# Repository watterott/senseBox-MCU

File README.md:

# senseBox MCU
senseBox MCU is a Microchip SAMD21 based open-source board for sensors.

* [Microchip ATSAMD21](https://www.microchip.com/wwwproducts/en/ATSAMD21G18) ARM Cortex-M0+ Microcontroller
* [Microchip ATECC608A](https://www.microchip.com/wwwproducts/en/ATECC608A) Crypto Authentication
* [Bosch BMX055](https://www.bosch-sensortec.com/bst/products/all_products/bmx055) Orientation Sensor (Accelerometer + Gyroscope + Magnetometer)
* USB CDC+MSC Bootloader (Arduino compatible)
* XBee compatible sockets (with UART and SPI)
* 5V tolerant IOs, UART, I2C (JST-PH connectors)
* MicroUSB connector for power and data
* Idle power consumption about 20mA (single 5V power supply)
* Open-Source
* **[Documentation on learn.watterott.com](https://learn.watterott.com)**

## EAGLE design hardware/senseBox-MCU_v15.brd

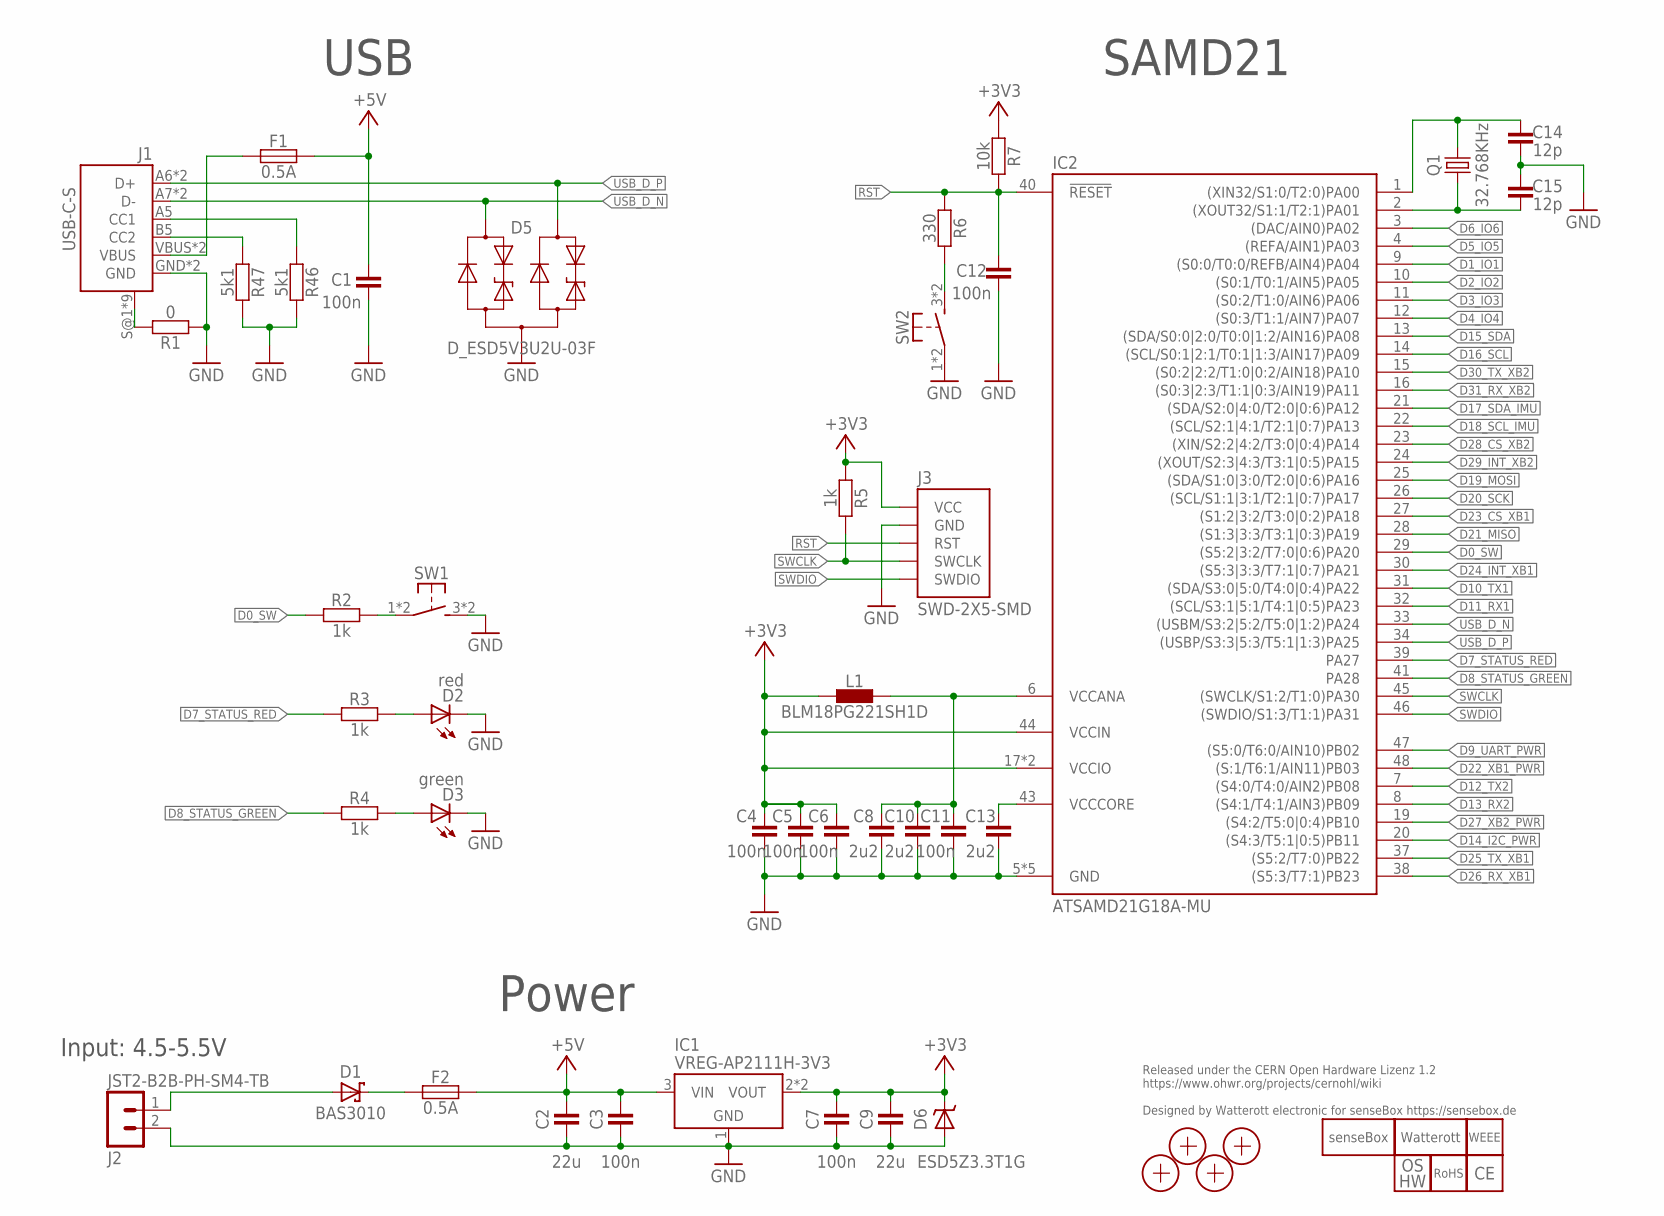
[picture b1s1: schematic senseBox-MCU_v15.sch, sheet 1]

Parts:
C1, C3, C4, C5, C6, C7, C11, C12: 100n; C0402
C2, C9: 22u; C0805
C8, C10, C13: 2u2; C0402
C14, C15: 12p; C0402
D1: BAS3010; SOD323
D2: red; C0603
D3: green; C0603
D5: D_ESD5V3U2U-03F; SOT723
D6: ESD5Z3.3T1G; SOD523
F1, F2: 0.5A; C0805
IC1: VREG-AP2111H-3V3; SOT223
IC2: ATSAMD21G18A-MU; QFN48-PAD
J1: USB-C-S
J2: JST2-B2B-PH-SM4-TB; JST_B2B-PH-SM4-TB
J3: SWD-2X5-SMD; SWD-2X5_SMD
L1: BLM18PG221SH1D; C0603
LOGO1: LOGO_SENSEBOX-12; SB_12MM
LOGO3: OSHW_LOGOX0070; OSHW_3MM
LOGO4: LOGO_SPARK-4; SPARK_4MM
LOGO5: LOGO_ROHS-4; ROHS_4MM
LOGO6: LOGO_WEEE-4; WEEE_4MM
LOGO7: LOGO_CE-4; CE_4MM
Q1: 32.768KHz; CRYSTAL_ZM315
R1: 0; C0402
R2, R3, R4, R5: 1k; C0402
R6: 330; C0402
R7: 10k; C0402
R46, R47: 5k1; C0402
SW1: PTS645SH50SMTR92-Grey; SW6X6_SMD
SW2: PTS645SK50SMTR92-Red; SW6X6_SMD
X1, X2, X3, X4: PASSER-07; PASSER_07MM

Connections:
+3V3: C4.2, C5.2, C6.2, C7.2, C9.2, D6.C, IC1.2 (VOUT), IC1.4 (VOUT), IC2.17 (VCCIO), IC2.36 (VCCIO), IC2.44 (VCCIN), J3.VCC, L1.1, R5.1, R7.1; also elsewhere on the board
+5V: C1.2, C2.2, C3.2, F1.2, F2.2, IC1.3 (VIN); also elsewhere on the board
CC1: J1.A5 (CC1), R46.1
CC2: J1.B5 (CC2), R47.1
D0_SW: IC2.29 ((S5:2|3:2/T7:0|0:6)PA20), R2.1
D1_IO1: IC2.9 ((S0:0/T0:0/REFB/AIN4)PA04); also elsewhere on the board
D2_IO2: IC2.10 ((S0:1/T0:1/AIN5)PA05); also elsewhere on the board
D3_IO3: IC2.11 ((S0:2/T1:0/AIN6)PA06); also elsewhere on the board
D4_IO4: IC2.12 ((S0:3/T1:1/AIN7)PA07); also elsewhere on the board
D5_IO5: IC2.4 ((REFA/AIN1)PA03); also elsewhere on the board
D6_IO6: IC2.3 ((DAC/AIN0)PA02); also elsewhere on the board
D7_STATUS_RED: IC2.39 (PA27), R3.1
D8_STATUS_GREEN: IC2.41 (PA28), R4.1
D9_UART_PWR: IC2.47 ((S5:0/T6:0/AIN10)PB02); also elsewhere on the board
D10_TX1: IC2.31 ((SDA/S3:0|5:0/T4:0|0:4)PA22); also elsewhere on the board
D11_RX1: IC2.32 ((SCL/S3:1|5:1/T4:1|0:5)PA23); also elsewhere on the board
D12_TX2: IC2.7 ((S4:0/T4:0/AIN2)PB08); also elsewhere on the board
D13_RX2: IC2.8 ((S4:1/T4:1/AIN3)PB09); also elsewhere on the board
D14_I2C_PWR: IC2.20 ((S4:3/T5:1|0:5)PB11); also elsewhere on the board
D15_SDA: IC2.13 ((SDA/S0:0|2:0/T0:0|1:2/AIN16)PA08); also elsewhere on the board
D16_SCL: IC2.14 ((SCL/S0:1|2:1/T0:1|1:3/AIN17)PA09); also elsewhere on the board
D17_SDA_IMU: IC2.21 ((SDA/S2:0|4:0/T2:0|0:6)PA12); also elsewhere on the board
D18_SCL_IMU: IC2.22 ((SCL/S2:1|4:1/T2:1|0:7)PA13); also elsewhere on the board
D19_MOSI: IC2.25 ((SDA/S1:0|3:0/T2:0|0:6)PA16); also elsewhere on the board
D20_SCK: IC2.26 ((SCL/S1:1|3:1/T2:1|0:7)PA17); also elsewhere on the board
D21_MISO: IC2.28 ((S1:3|3:3/T3:1|0:3)PA19); also elsewhere on the board
D22_!XB1_PWR: IC2.48 ((S:1/T6:1/AIN11)PB03); also elsewhere on the board
D23_CS_XB1: IC2.27 ((S1:2|3:2/T3:0|0:2)PA18); also elsewhere on the board
D24_INT_XB1: IC2.30 ((S5:3|3:3/T7:1|0:7)PA21); also elsewhere on the board
D25_TX_XB1: IC2.37 ((S5:2/T7:0)PB22); also elsewhere on the board
D26_RX_XB1: IC2.38 ((S5:3/T7:1)PB23); also elsewhere on the board
D27_!XB2_PWR: IC2.19 ((S4:2/T5:0|0:4)PB10); also elsewhere on the board
D28_CS_XB2: IC2.23 ((XIN/S2:2|4:2/T3:0|0:4)PA14); also elsewhere on the board
D29_INT_XB2: IC2.24 ((XOUT/S2:3|4:3/T3:1|0:5)PA15); also elsewhere on the board
D30_TX_XB2: IC2.15 ((S0:2|2:2/T1:0|0:2/AIN18)PA10); also elsewhere on the board
D31_RX_XB2: IC2.16 ((S0:3|2:3/T1:1|0:3/AIN19)PA11); also elsewhere on the board
GND: C1.1, C2.1, C3.1, C4.1, C5.1, C6.1, C7.1, C8.1, C9.1, C10.1, C11.1, C12.1, C13.1, C14.2, C15.1, D2.C, D3.C, D5.3 (A), D6.A, IC1.1 (GND), IC2.5 (GND), IC2.18 (GND), IC2.35 (GND), IC2.42 (GND), IC2.TP (GND), J1.GND, J1.GND2 (GND), J2.2, J3.GND@1 (GND), J3.GND@2 (GND), J3.GND@3 (GND), R1.1, R46.2, R47.2, SW1.3 (S1), SW1.4 (S1), SW2.1, SW2.2 (P1); also elsewhere on the board
unnamed: C14.1, IC2.1 ((XIN32/S1:0/T2:0)PA00), Q1.2
unnamed: C15.2, IC2.2 ((XOUT32/S1:1/T2:1)PA01), Q1.1
unnamed: D2.A, R3.2
unnamed: D3.A, R4.2
unnamed: R6.2, SW2.3 (S1), SW2.4 (S1)
RST: C12.2, IC2.40 (!RESET), J3.RST, R6.1, R7.2
SHLD: J1.S@1 (SHIELD), J1.S@2 (SHIELD), J1.S@3 (SHIELD), J1.S@4 (SHIELD), J1.S@5 (SHIELD), J1.S@6 (SHIELD), J1.S@7 (SHIELD), J1.S@8 (SHIELD), J1.S@9 (SHIELD), R1.2
SW: R2.2, SW1.1, SW1.2 (P1)
SWCLK: IC2.45 ((SWCLK/S1:2/T1:0)PA30), J3.SWCLK, R5.2
SWDIO: IC2.46 ((SWDIO/S1:3/T1:1)PA31), J3.SWDIO
USB_D_N: D5.1 (C1), IC2.33 ((USBM/S3:2|5:2/T5:0|1:2)PA24), J1.A7 (D-), J1.B7 (D-)
USB_D_P: D5.2 (C2), IC2.34 ((USBP/S3:3|5:3/T5:1|1:3)PA25), J1.A6 (D+), J1.B6 (D+)
V5V: D1.C, F2.1
VBUS: F1.1, J1.VBUS, J1.VBUS2 (VBUS)
VCCANA: C8.2, C10.2, C11.2, IC2.6 (VCCANA), L1.2
VCCCORE: C13.2, IC2.43 (VCCCORE)
VIN: D1.A, J2.1

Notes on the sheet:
Released under the CERN Open Hardware Lizenz 1.2 https://www.ohwr.org/projects/cernohl/wiki Designed by Watterott electronic for senseBox https://sensebox.de
USB
SAMD21
Power
Input: 4.5-5.5V

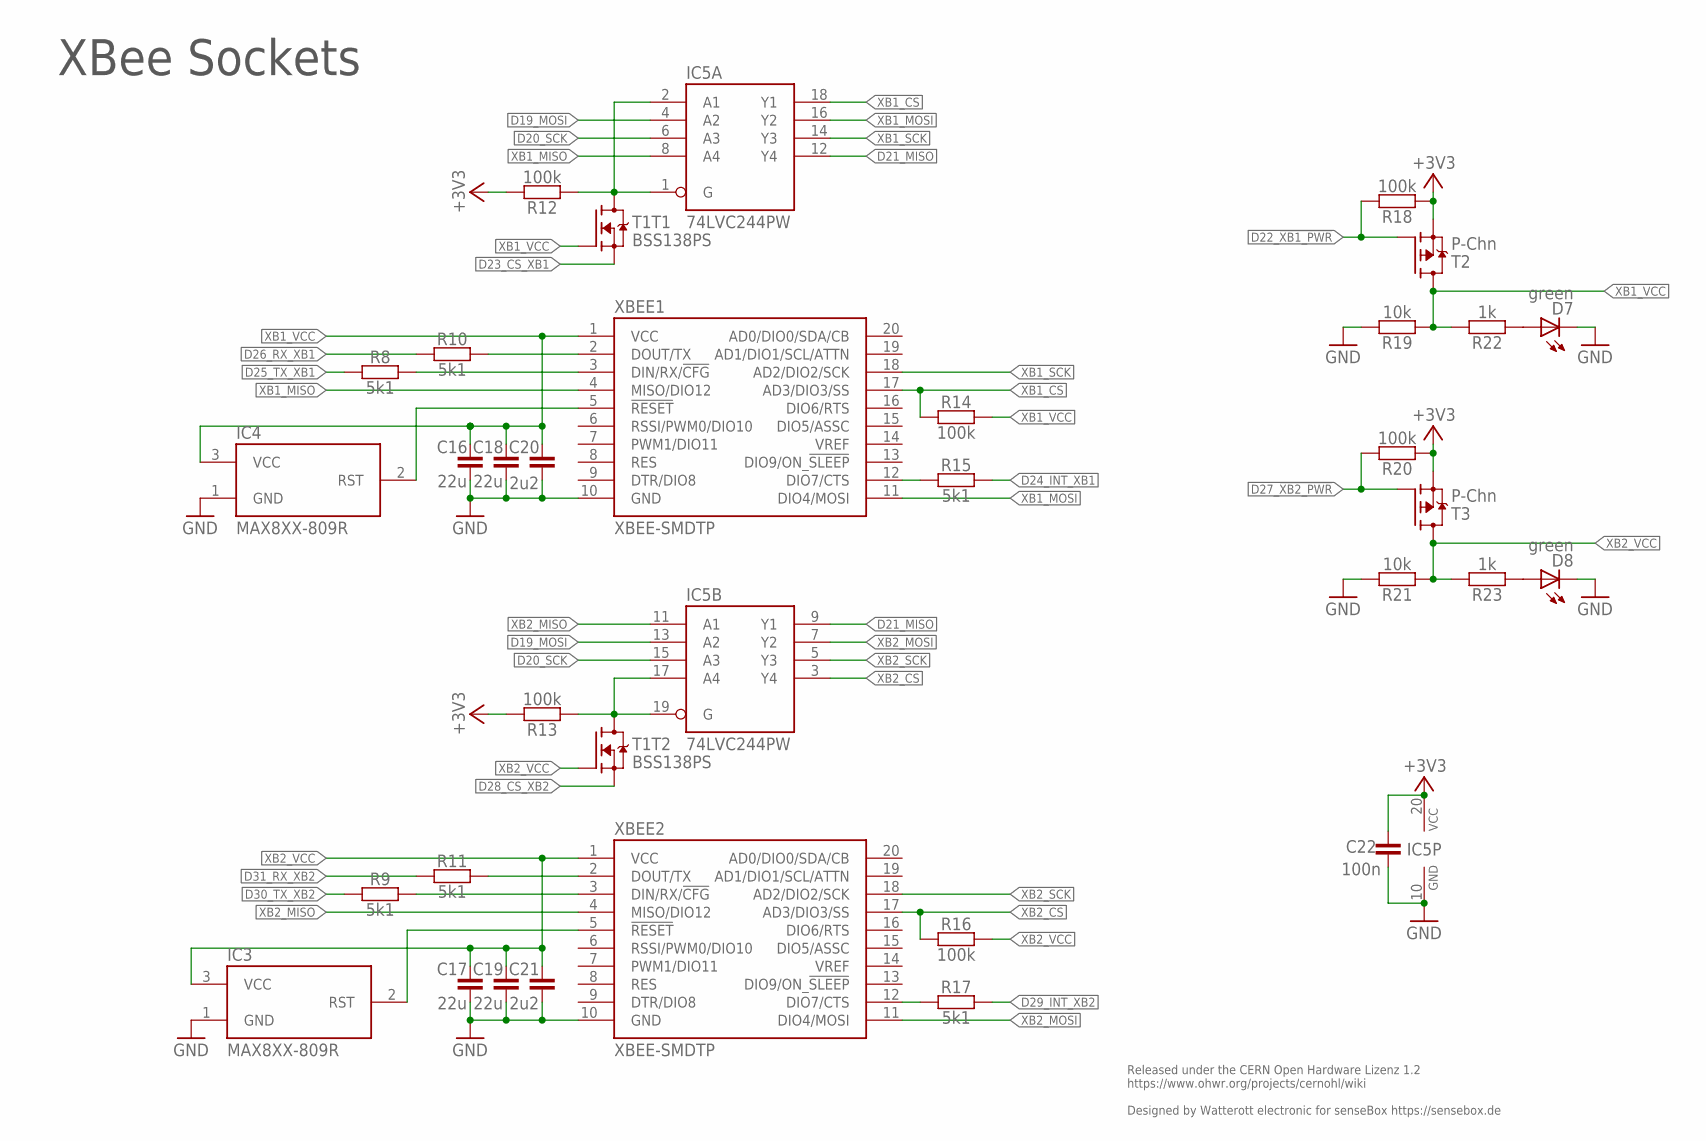
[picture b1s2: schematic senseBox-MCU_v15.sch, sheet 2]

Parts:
C16, C17, C18, C19: 22u; C0805
C20, C21: 2u2; C0402
C22: 100n; C0402
D7, D8: green; C0603
IC3, IC4: MAX8XX-809R; SOT23
IC5: 74LVC244PW; TSSOP20
R8, R9, R10, R11, R15, R17: 5k1; C0402
R12, R13, R14, R16, R18, R20: 100k; C0402
R19, R21: 10k; C0402
R22, R23: 1k; C0402
T1: BSS138PS; SOT363
T2, T3: P-Chn; SOT23
XBEE1, XBEE2: XBEE-SMDTP; XBEE_SMD_TP

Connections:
+3V3: C22.2, IC5.20 (VCC), R12.2, R13.2, R18.1, R20.1, T2.2 (S), T3.2 (S); also elsewhere on the board
D19_MOSI: IC5.4 (A2), IC5.13 (A2); also elsewhere on the board
D20_SCK: IC5.6 (A3), IC5.15 (A3); also elsewhere on the board
D21_MISO: IC5.9 (Y1), IC5.12 (Y4); also elsewhere on the board
D22_!XB1_PWR: R18.2, T2.1 (G); also elsewhere on the board
D23_CS_XB1: T1.1 (S); also elsewhere on the board
D24_INT_XB1: R15.2; also elsewhere on the board
D25_TX_XB1: R8.1; also elsewhere on the board
D26_RX_XB1: R10.1; also elsewhere on the board
D27_!XB2_PWR: R20.2, T3.1 (G); also elsewhere on the board
D28_CS_XB2: T1.4 (S); also elsewhere on the board
D29_INT_XB2: R17.2; also elsewhere on the board
D30_TX_XB2: R9.1; also elsewhere on the board
D31_RX_XB2: R11.1; also elsewhere on the board
GND: C16.1, C17.1, C18.1, C19.1, C20.1, C21.1, C22.1, D7.C, D8.C, IC3.1 (GND), IC4.1 (GND), IC5.10 (GND), R19.2, R21.2, XBEE1.10 (GND), XBEE2.10 (GND); also elsewhere on the board
MCU_CS_XBEE1: IC5.1 (G), IC5.2 (A1), R12.1, T1.6 (D)
MCU_CS_XBEE2: IC5.17 (A4), IC5.19 (G), R13.1, T1.3 (D)
unnamed: D7.A, R22.1
unnamed: D8.A, R23.1
RST_XB1: IC4.2 (RST), XBEE1.5 (!RESET!)
RST_XB2: IC3.2 (RST), XBEE2.5 (!RESET!)
XB1_CS: IC5.18 (Y1), R14.1, XBEE1.17 (AD3/DIO3/SS)
XB1_MISO: IC5.8 (A4), XBEE1.4 (MISO/DIO12)
XB1_MOSI: IC5.16 (Y2), XBEE1.11 (DIO4/MOSI)
XB1_RX: R8.2, XBEE1.3 (DIN/RX/!CFG!)
XB1_SCK: IC5.14 (Y3), XBEE1.18 (AD2/DIO2/SCK)
XB1_TX: R10.2, XBEE1.2 (DOUT/TX)
XB1_VCC: C16.2, C18.2, C20.2, IC4.3 (VCC), R14.2, R19.1, R22.2, T1.2 (G), T2.3 (D), XBEE1.1 (VCC)
XB2_CS: IC5.3 (Y4), R16.1, XBEE2.17 (AD3/DIO3/SS)
XB2_MISO: IC5.11 (A1), XBEE2.4 (MISO/DIO12)
XB2_MOSI: IC5.7 (Y2), XBEE2.11 (DIO4/MOSI)
XB2_RX: R9.2, XBEE2.3 (DIN/RX/!CFG!)
XB2_SCK: IC5.5 (Y3), XBEE2.18 (AD2/DIO2/SCK)
XB2_TX: R11.2, XBEE2.2 (DOUT/TX)
XB2_VCC: C17.2, C19.2, C21.2, IC3.3 (VCC), R16.2, R21.1, R23.2, T1.5 (G), T3.3 (D), XBEE2.1 (VCC)
XBEE1_CTS/IRQ: R15.1, XBEE1.12 (DIO7/CTS)
XBEE2_CTS/IRQ: R17.1, XBEE2.12 (DIO7/CTS)

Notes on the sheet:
Released under the CERN Open Hardware Lizenz 1.2 https://www.ohwr.org/projects/cernohl/wiki Designed by Watterott electronic for senseBox https://sensebox.de
XBee Sockets

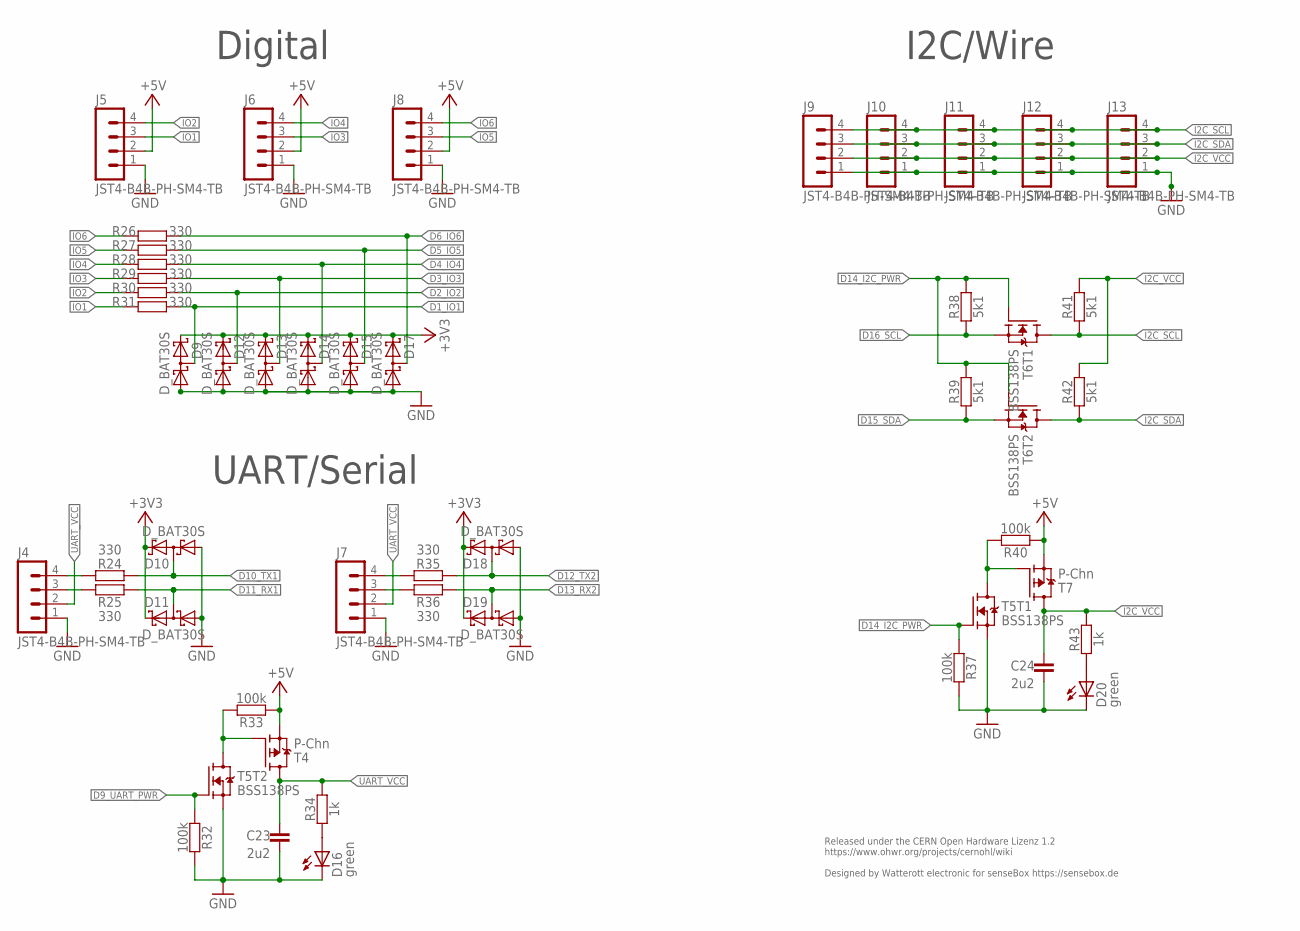
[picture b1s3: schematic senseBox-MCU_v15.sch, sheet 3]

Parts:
C23, C24: 2u2; C0402
D9, D10, D11, D12, D13, D14, D15, D17, D18, D19: D_BAT30S; SOT323
D16, D20: green; C0603
J4, J5, J6, J7, J8, J9, J10, J11, J12, J13: JST4-B4B-PH-SM4-TB; JST_B4B-PH-SM4-TB
R24, R25, R26, R27, R28, R29, R30, R31, R35, R36: 330; C0402
R32, R33, R37, R40: 100k; C0402
R34, R43: 1k; C0402
R38, R39, R41, R42: 5k1; C0402
T4, T7: P-Chn; SOT23
T5, T6: BSS138PS; SOT363

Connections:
!I2C_POWER: R40.2, T5.6 (D), T7.1 (G)
!UART_POWER: R33.2, T4.1 (G), T5.3 (D)
+3V3: D9.2 (C), D10.2 (C), D11.2 (C), D12.2 (C), D13.2 (C), D14.2 (C), D15.2 (C), D17.2 (C), D18.2 (C), D19.2 (C); also elsewhere on the board
+5V: J5.2, J6.2, J8.2, R33.1, R40.1, T4.2 (S), T7.2 (S); also elsewhere on the board
D1_IO1: D9.3 (CA), R31.1; also elsewhere on the board
D2_IO2: D12.3 (CA), R30.1; also elsewhere on the board
D3_IO3: D13.3 (CA), R29.1; also elsewhere on the board
D4_IO4: D14.3 (CA), R28.1; also elsewhere on the board
D5_IO5: D15.3 (CA), R27.1; also elsewhere on the board
D6_IO6: D17.3 (CA), R26.1; also elsewhere on the board
D9_UART_PWR: R32.1, T5.5 (G); also elsewhere on the board
D10_TX1: D10.3 (CA), R24.1; also elsewhere on the board
D11_RX1: D11.3 (CA), R25.1; also elsewhere on the board
D12_TX2: D18.3 (CA), R35.1; also elsewhere on the board
D13_RX2: D19.3 (CA), R36.1; also elsewhere on the board
D14_I2C_PWR: R37.1, R38.2, R39.2, T5.2 (G), T6.2 (G), T6.5 (G); also elsewhere on the board
D15_SDA: R39.1, T6.4 (S); also elsewhere on the board
D16_SCL: R38.1, T6.1 (S); also elsewhere on the board
GND: C23.1, C24.1, D9.1 (A), D10.1 (A), D11.1 (A), D12.1 (A), D13.1 (A), D14.1 (A), D15.1 (A), D16.C, D17.1 (A), D18.1 (A), D19.1 (A), D20.C, J4.1, J5.1, J6.1, J7.1, J8.1, J9.1, J10.1, J11.1, J12.1, J13.1, R32.2, R37.2, T5.1 (S), T5.4 (S); also elsewhere on the board
I2C_SCL: J9.4, J10.4, J11.4, J12.4, J13.4, R41.1, T6.6 (D)
I2C_SDA: J9.3, J10.3, J11.3, J12.3, J13.3, R42.1, T6.3 (D)
I2C_VCC: C24.2, J9.2, J10.2, J11.2, J12.2, J13.2, R41.2, R42.2, R43.2, T7.3 (D)
IO1: J5.3, R31.2
IO2: J5.4, R30.2
IO3: J6.3, R29.2
IO4: J6.4, R28.2
IO5: J8.3, R27.2
IO6: J8.4, R26.2
unnamed: D20.A, R43.1
unnamed: D16.A, R34.1
UART_RX1: J4.3, R25.2
UART_RX2: J7.3, R36.2
UART_TX1: J4.4, R24.2
UART_TX2: J7.4, R35.2
UART_VCC: C23.2, J4.2, J7.2, R34.2, T4.3 (D)

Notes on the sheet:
Released under the CERN Open Hardware Lizenz 1.2 https://www.ohwr.org/projects/cernohl/wiki Designed by Watterott electronic for senseBox https://sensebox.de
Digital
I2C/Wire
UART/Serial

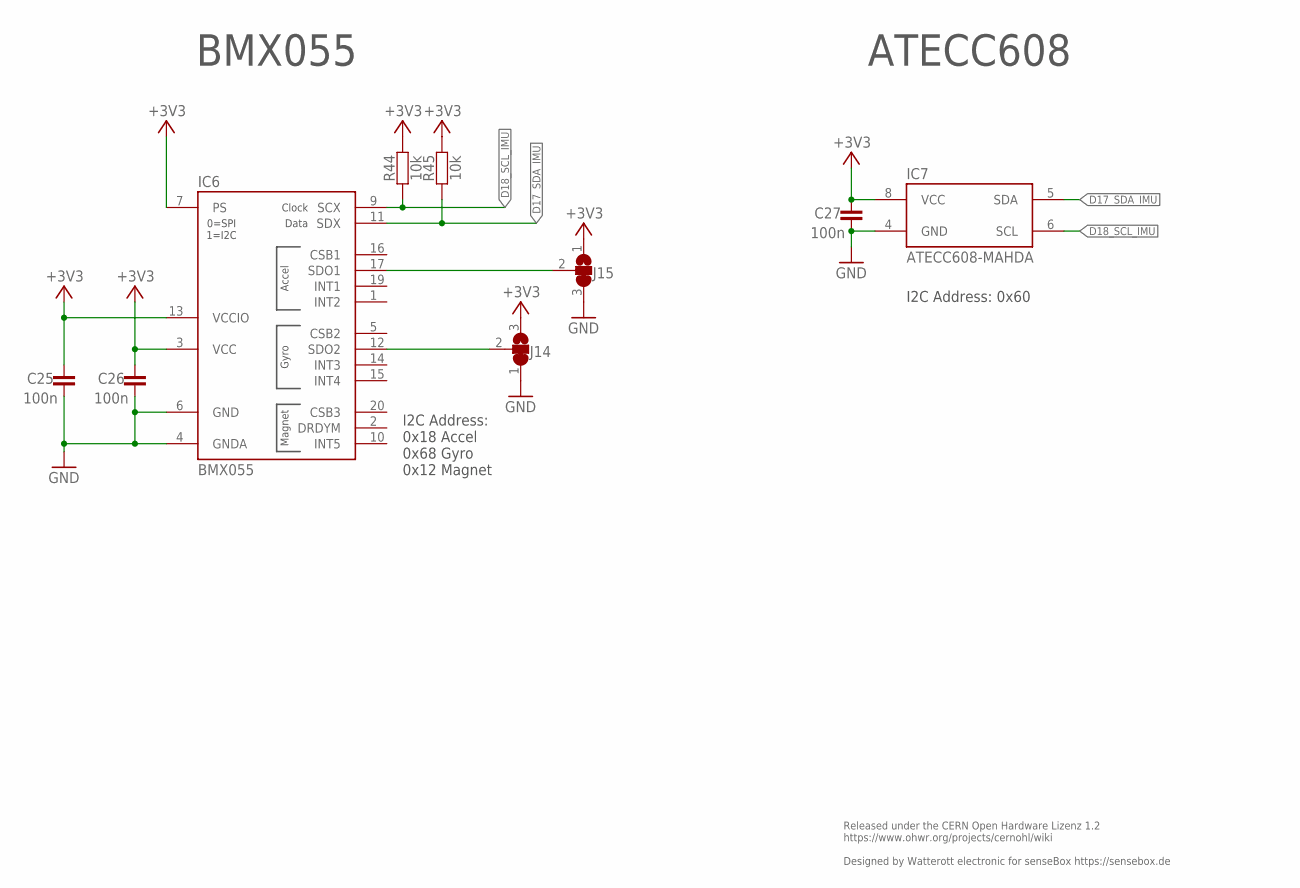
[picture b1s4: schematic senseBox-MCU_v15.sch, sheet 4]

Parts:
C25, C26, C27: 100n; C0402
IC6: BMX055
IC7: ATECC608-MAHDA; UDFN8
J14, J15: JUMPER3-0402
R44, R45: 10k; C0402

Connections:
+3V3: C25.2, C26.2, C27.2, IC6.3 (VCC), IC6.7 (PS), IC6.13 (VCCIO), IC7.8 (VCC), J14.3, J15.1, R44.2, R45.2; also elsewhere on the board
D17_SDA_IMU: IC6.11 (SDX), IC7.5 (SDA), R45.1; also elsewhere on the board
D18_SCL_IMU: IC6.9 (SCX), IC7.6 (SCL), R44.1; also elsewhere on the board
GND: C25.1, C26.1, C27.1, IC6.4 (GNDA), IC6.6 (GND), IC7.4 (GND), J14.1, J15.3; also elsewhere on the board
SDO1: IC6.17 (SDO1), J15.2
SDO2: IC6.12 (SDO2), J14.2

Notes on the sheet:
Released under the CERN Open Hardware Lizenz 1.2 https://www.ohwr.org/projects/cernohl/wiki Designed by Watterott electronic for senseBox https://sensebox.de
I2C Address: 0x18 Accel 0x68 Gyro 0x12 Magnet
I2C Address: 0x60
BMX055
ATECC608

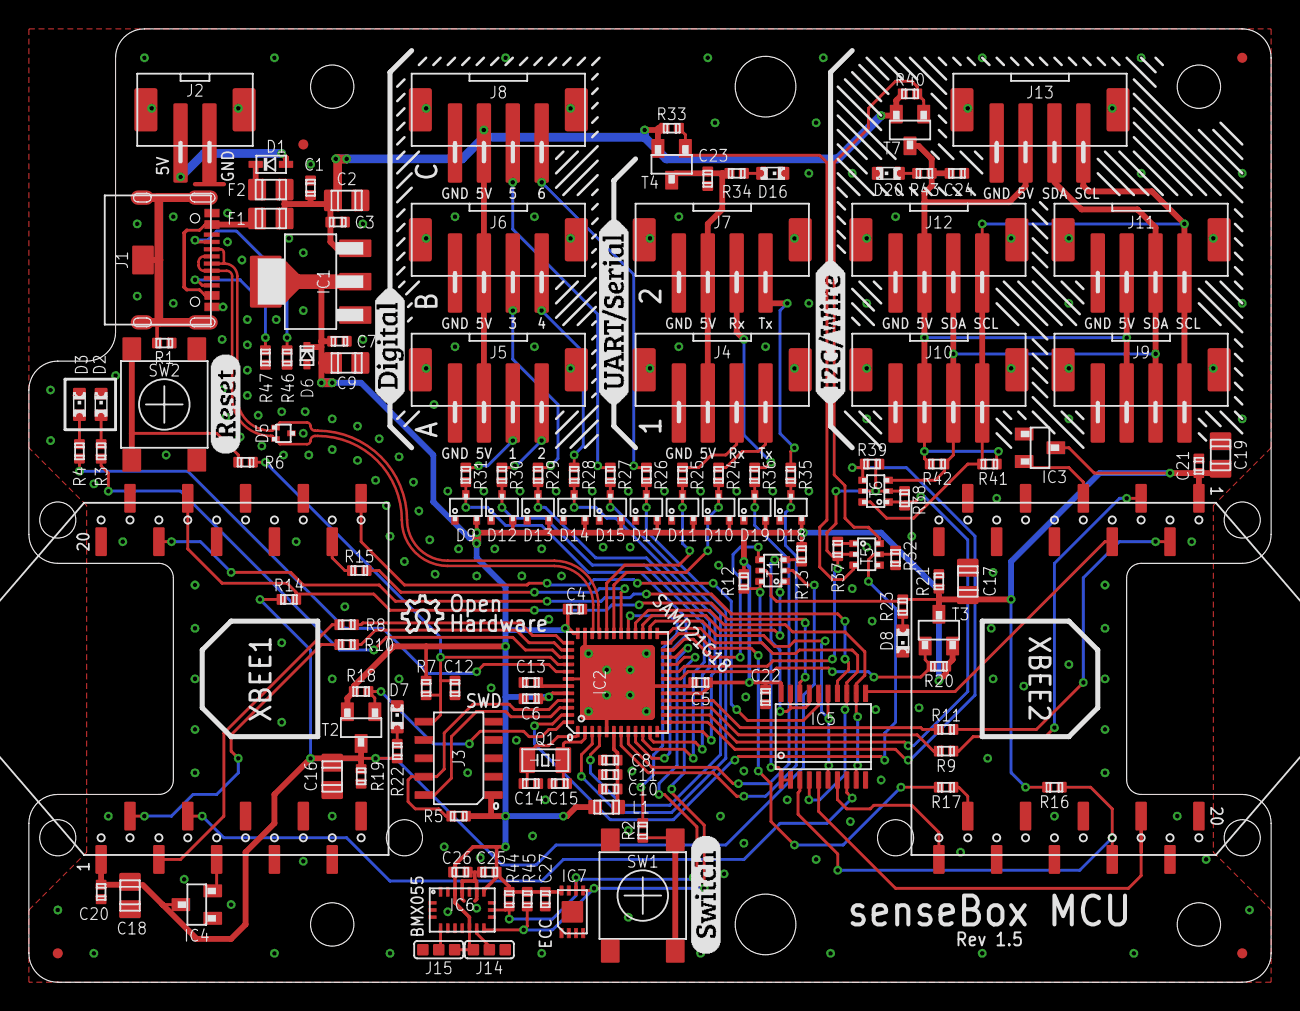
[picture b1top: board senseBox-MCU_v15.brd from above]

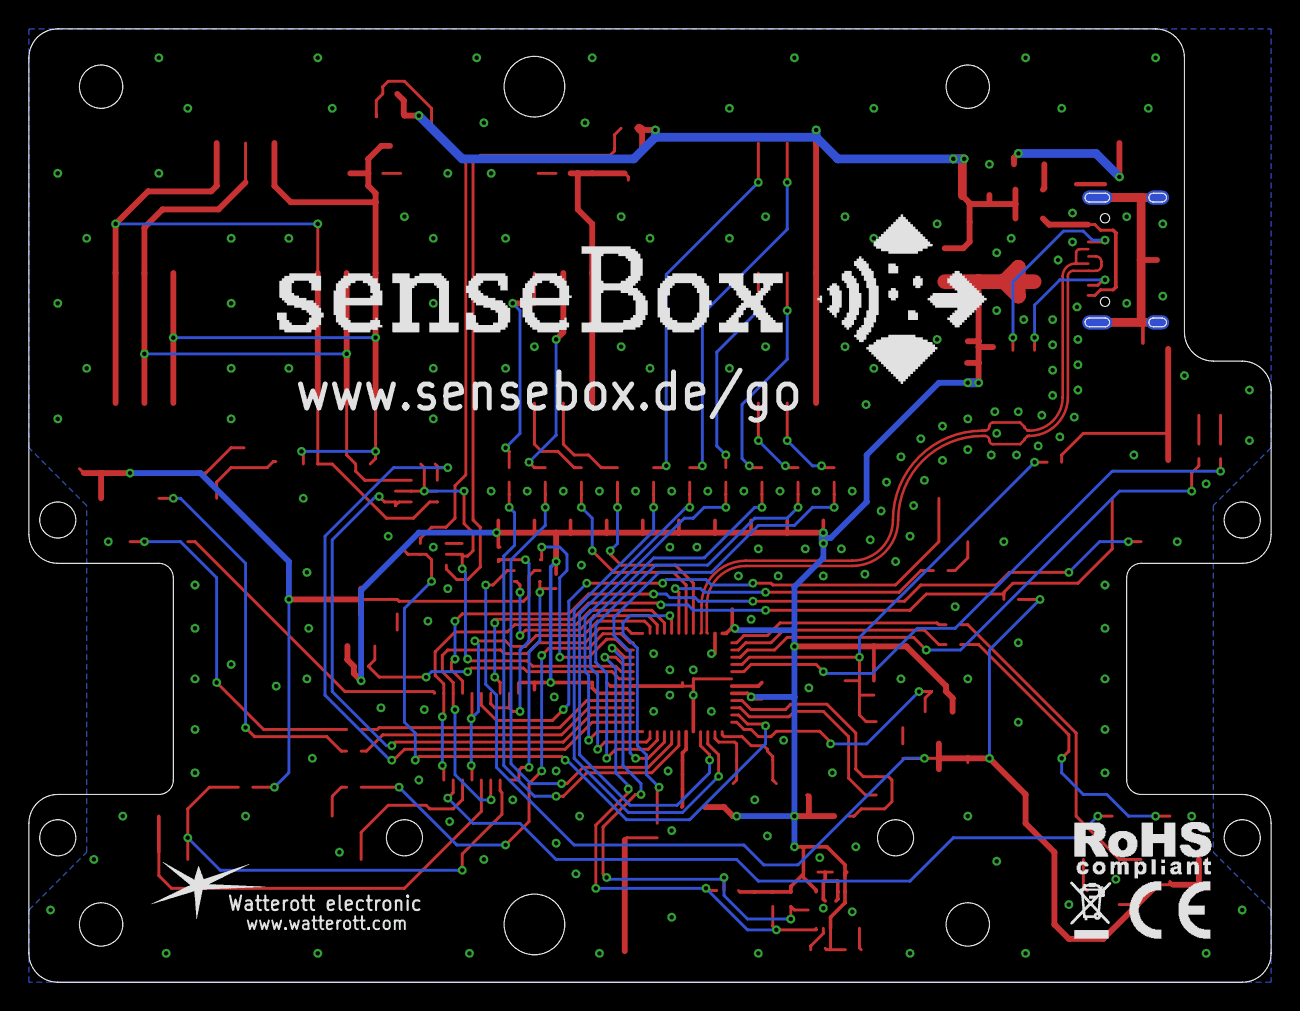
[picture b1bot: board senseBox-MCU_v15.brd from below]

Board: 2 copper layers, 86.0 x 66.0 mm, 140 parts (5 on the bottom side), 96 nets.

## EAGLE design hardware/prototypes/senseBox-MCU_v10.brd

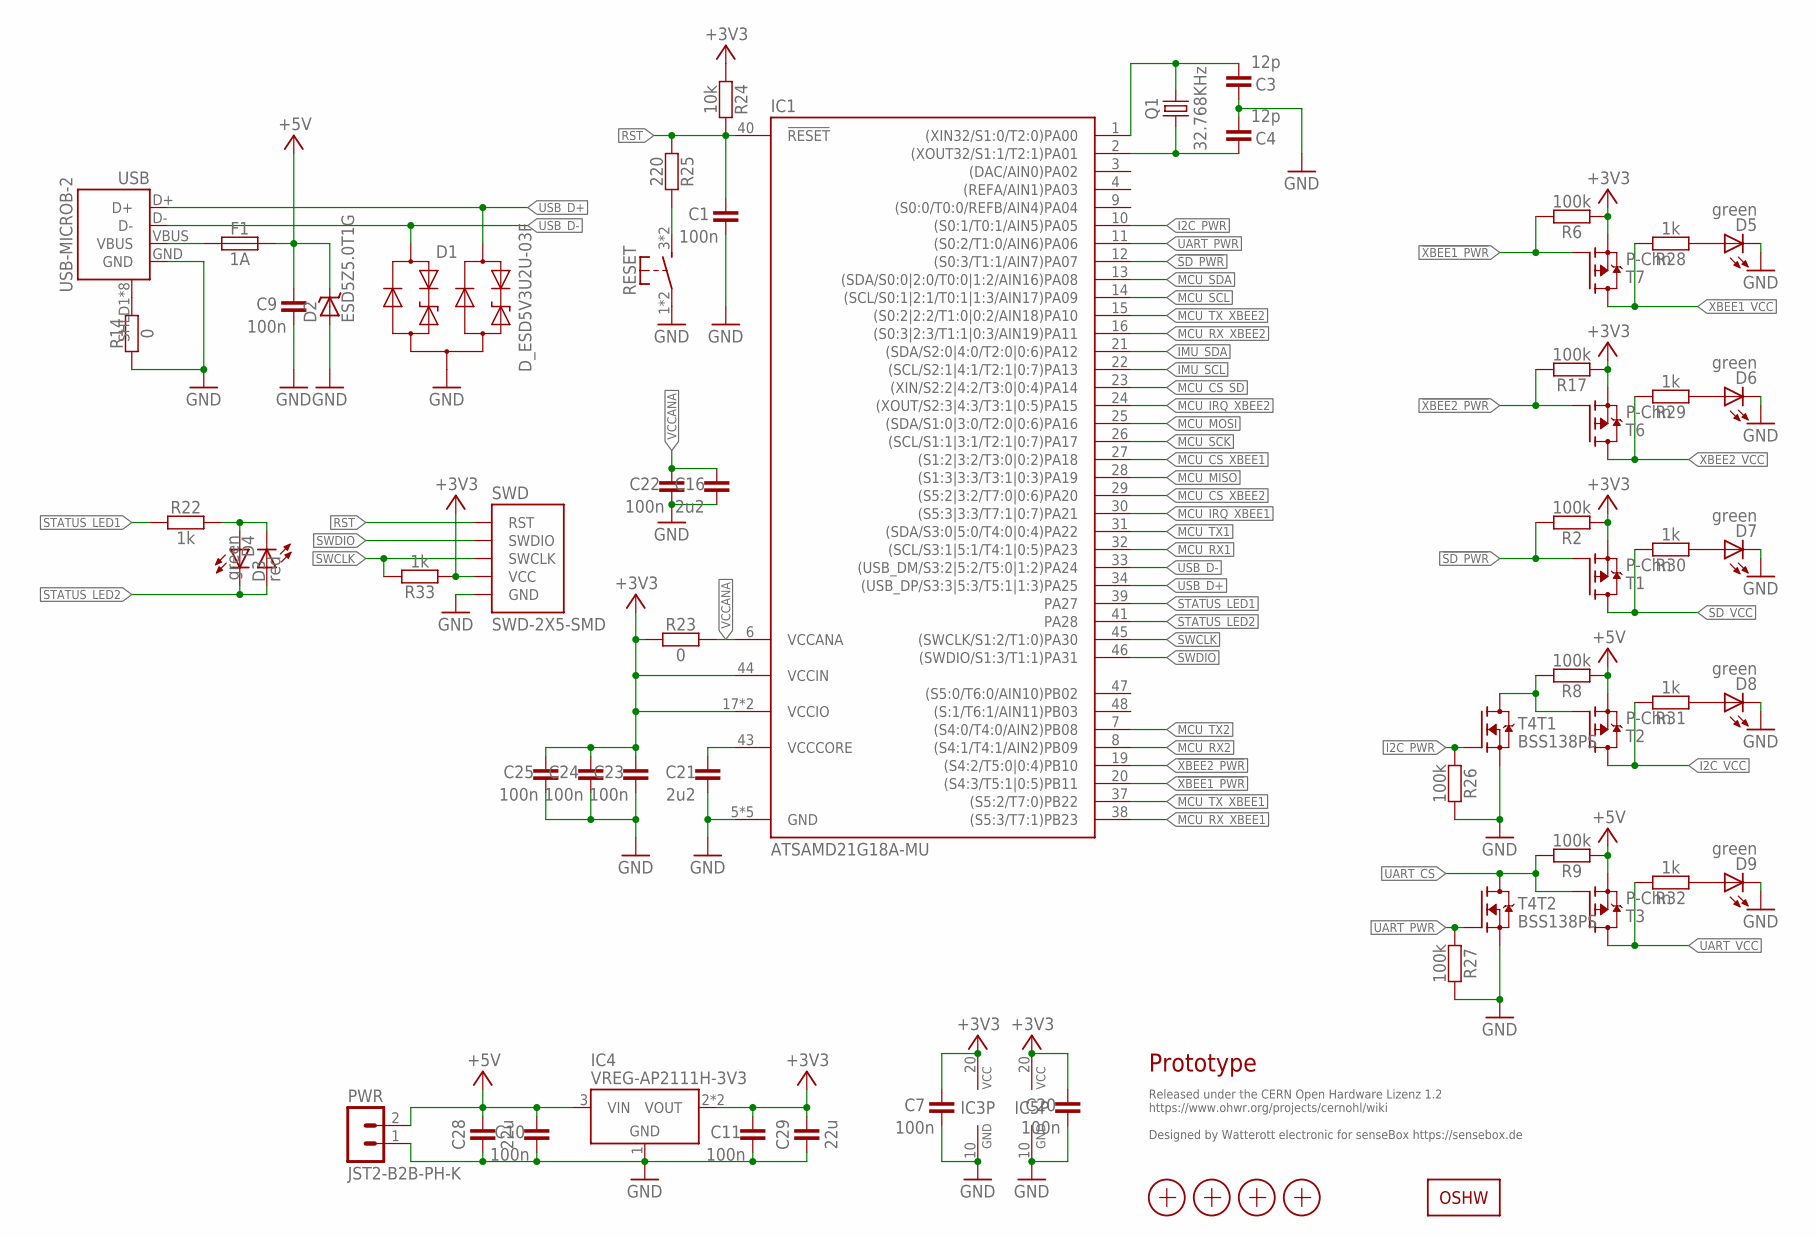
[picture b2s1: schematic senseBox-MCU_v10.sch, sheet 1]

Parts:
C1, C7, C9, C10, C11, C20, C22, C23, C24, C25: 100n; C0402
C3, C4: 12p; C0402
C16, C21: 2u2; C0402
C28, C29: 22u; C0805
D1: D_ESD5V3U2U-03F; SOT723
D2: ESD5Z5.0T1G; SOD523
D3: red; C0603
D4, D5, D6, D7, D8, D9: green; C0603
F1: 1A; C0805
IC1: ATSAMD21G18A-MU; QFN48-PAD
IC3, IC5: 74LVC244PW; TSSOP20
IC4: VREG-AP2111H-3V3; SOT223
LOGO2: OSHW_LOGOX0070; OSHW_6X70
PWR: JST2-B2B-PH-K; JST_B2B-PH-K
Q1: 32.768KHz; CRYSTAL_ZM315
R2, R6, R8, R9, R17, R26, R27: 100k; C0402
R14, R23: 0; C0402
R22, R28, R29, R30, R31, R32, R33: 1k; C0402
R24: 10k; C0402
R25: 220; C0402
RESET: SW-TACTILE-PTS840P; PTS840P
SWD: SWD-2X5-SMD; SWD-2X5_SMD
T1, T2, T3, T6, T7: P-Chn; SOT23
T4: BSS138PS; SOT363
USB: USB-MICROB-2; USB-MICROB-10118194
X1, X2, X3, X4: PASSER-07; PASSER_07MM

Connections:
!I2C_POWER: R8.2, T2.1 (G), T4.6 (D)
!SD_PWR: IC1.12 ((S0:3/T1:1/AIN7)PA07), R2.2, T1.1 (G)
!XBEE1_PWR: IC1.20 ((S4:3/T5:1|0:5)PB11), R6.2, T7.1 (G)
!XBEE2_PWR: IC1.19 ((S4:2/T5:0|0:4)PB10), R17.2, T6.1 (G)
+3V3: C7.2, C11.2, C20.2, C23.2, C24.2, C25.2, C29.2, IC1.17 (VCCIO), IC1.36 (VCCIO), IC1.44 (VCCIN), IC3.20 (VCC), IC4.2 (VOUT), IC4.4 (VOUT), IC5.20 (VCC), R2.1, R6.1, R17.1, R23.1, R24.1, R33.1, SWD.VCC, T1.2 (S), T6.2 (S), T7.2 (S); also elsewhere on the board
+5V: C9.2, C10.2, C28.2, D2.C, F1.2, IC4.3 (VIN), PWR.2, R8.1, R9.1, T2.2 (S), T3.2 (S)
GND: C1.1, C3.2, C4.1, C7.1, C9.1, C10.1, C11.1, C16.1, C20.1, C21.1, C22.1, C23.1, C24.1, C25.1, C28.1, C29.1, D1.3 (A), D2.A, D5.C, D6.C, D7.C, D8.C, D9.C, IC1.5 (GND), IC1.18 (GND), IC1.35 (GND), IC1.42 (GND), IC1.TP (GND), IC3.10 (GND), IC4.1 (GND), IC5.10 (GND), PWR.1, R14.1, R26.2, R27.2, RESET.1, RESET.2 (P1), SWD.GND@1 (GND), SWD.GND@2 (GND), SWD.GND@3 (GND), T4.1 (S), T4.4 (S), USB.GND; also elsewhere on the board
I2C_PWR: IC1.10 ((S0:1/T0:1/AIN5)PA05), R26.1, T4.2 (G)
I2C_VCC: R31.2, T2.3 (D); also elsewhere on the board
IMU_SCL: IC1.22 ((SCL/S2:1|4:1/T2:1|0:7)PA13); also elsewhere on the board
IMU_SDA: IC1.21 ((SDA/S2:0|4:0/T2:0|0:6)PA12); also elsewhere on the board
MCU_CS_SD: IC1.23 ((XIN/S2:2|4:2/T3:0|0:4)PA14); also elsewhere on the board
MCU_CS_XBEE1: IC1.27 ((S1:2|3:2/T3:0|0:2)PA18); also elsewhere on the board
MCU_CS_XBEE2: IC1.29 ((S5:2|3:2/T7:0|0:6)PA20); also elsewhere on the board
MCU_IRQ_XBEE1: IC1.30 ((S5:3|3:3/T7:1|0:7)PA21); also elsewhere on the board
MCU_IRQ_XBEE2: IC1.24 ((XOUT/S2:3|4:3/T3:1|0:5)PA15); also elsewhere on the board
MCU_MISO: IC1.28 ((S1:3|3:3/T3:1|0:3)PA19); also elsewhere on the board
MCU_MOSI: IC1.25 ((SDA/S1:0|3:0/T2:0|0:6)PA16); also elsewhere on the board
MCU_RX1: IC1.32 ((SCL/S3:1|5:1/T4:1|0:5)PA23); also elsewhere on the board
MCU_RX2: IC1.8 ((S4:1/T4:1/AIN2)PB09); also elsewhere on the board
MCU_RX_XBEE1: IC1.38 ((S5:3/T7:1)PB23); also elsewhere on the board
MCU_RX_XBEE2: IC1.16 ((S0:3|2:3/T1:1|0:3/AIN19)PA11); also elsewhere on the board
MCU_SCK: IC1.26 ((SCL/S1:1|3:1/T2:1|0:7)PA17); also elsewhere on the board
MCU_SCL: IC1.14 ((SCL/S0:1|2:1/T0:1|1:3/AIN17)PA09); also elsewhere on the board
MCU_SDA: IC1.13 ((SDA/S0:0|2:0/T0:0|1:2/AIN16)PA08); also elsewhere on the board
MCU_TX1: IC1.31 ((SDA/S3:0|5:0/T4:0|0:4)PA22); also elsewhere on the board
MCU_TX2: IC1.7 ((S4:0/T4:0/AIN2)PB08); also elsewhere on the board
MCU_TX_XBEE1: IC1.37 ((S5:2/T7:0)PB22); also elsewhere on the board
MCU_TX_XBEE2: IC1.15 ((S0:2|2:2/T1:0|0:2/AIN18)PA10); also elsewhere on the board
unnamed: C3.1, IC1.1 ((XIN32/S1:0/T2:0)PA00), Q1.2
unnamed: C4.2, IC1.2 ((XOUT32/S1:1/T2:1)PA01), Q1.1
unnamed: D5.A, R28.1
unnamed: D6.A, R29.1
unnamed: D7.A, R30.1
unnamed: D8.A, R31.1
unnamed: D9.A, R32.1
unnamed: D3.A, D4.C, R22.2
unnamed: R25.2, RESET.3 (S1), RESET.4 (S1)
RST: C1.2, IC1.40 (!RESET), R24.2, R25.1, SWD.RST
SD_VCC: R30.2, T1.3 (D); also elsewhere on the board
SHLD: R14.2, USB.SHLD1 (SHIELD), USB.SHLD2 (SHIELD), USB.SHLD3 (SHIELD), USB.SHLD4 (SHIELD), USB.SHLD5 (SHIELD), USB.SHLD6 (SHIELD), USB.SHLD7 (SHIELD), USB.SHLD8 (SHIELD)
STATUS_LED1: IC1.39 (PA27), R22.1
STATUS_LED2: D3.C, D4.A, IC1.41 (PA28)
SWCLK: IC1.45 ((SWCLK/S1:2/T1:0)PA30), R33.2, SWD.SWCLK
SWDIO: IC1.46 ((SWDIO/S1:3/T1:1)PA31), SWD.SWDIO
UART_CS: R9.2, T3.1 (G), T4.3 (D); also elsewhere on the board
UART_PWR: IC1.11 ((S0:2/T1:0/AIN6)PA06), R27.1, T4.5 (G)
UART_VCC: R32.2, T3.3 (D); also elsewhere on the board
USB_D+: D1.2 (C2), IC1.34 ((USB_DP/S3:3|5:3/T5:1|1:3)PA25), USB.D+
USB_D-: D1.1 (C1), IC1.33 ((USB_DM/S3:2|5:2/T5:0|1:2)PA24), USB.D-
VBUS: F1.1, USB.VBUS
VCCANA: C16.2, C22.2, IC1.6 (VCCANA), R23.2
VCCCORE: C21.2, IC1.43 (VCCCORE)
XBEE1_VCC: R28.2, T7.3 (D); also elsewhere on the board
XBEE2_VCC: R29.2, T6.3 (D); also elsewhere on the board

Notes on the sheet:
Released under the CERN Open Hardware Lizenz 1.2 https://www.ohwr.org/projects/cernohl/wiki Designed by Watterott electronic for senseBox https://sensebox.de
Prototype
